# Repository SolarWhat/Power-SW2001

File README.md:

# Power-SW2001

Solar What?! is the outcome of ongoing research at the University of Edinburgh.

The product design process has taken place over three continents, with input from solar technicians, end users and energy access practitioners.

In 2017 over 6 million small, solar powered lighting devices were sold worldwide and 1.6 million solar powered lighting devices entered electronic waste flows.

We believe that delivering affordable, clean energy for all can also promote responsible production and consumption.

Our goal is to advocate for sustainable design in the global solar industry and promote the repair, reuse and recycling of solar powered electronics. We are pro-solar, anti-waste.

The Solar What?! Power is one of two products we have designed to champion our research and catalyse discussion around sustainability and repairability in the off-grid solar sector. The repository for our other product, the Solar What Light, can be found [here](https://github.com/SolarWhat/Light-SW1001 "here").

We encourage you to download the files, reproduce the products, make edits, suggest improvements and, most importantly, share your ideas around design for sustainable international development.  

More information about the project and the team behind it can be found on our [website](http://www.solarwhat.xyz/index.php "website").

You can get in touch with the team by emailing info@solarwhat.xyz. 

[User Manual and Tech Specs](http://www.solarwhat.xyz/resources.php "User Manual and Tech Specs")

[Gerber Files, BOM and Firmware Files](https://github.com/SolarWhat/Power-SW2001/tree/master/PCB%20Files "Gerber Files, BOM and Firmware Files")

[CAD Files (stp)](https://github.com/SolarWhat/Power-SW2001/blob/master/Solar%20What%20Power%20Assembly.stp "CAD Files (stp)")

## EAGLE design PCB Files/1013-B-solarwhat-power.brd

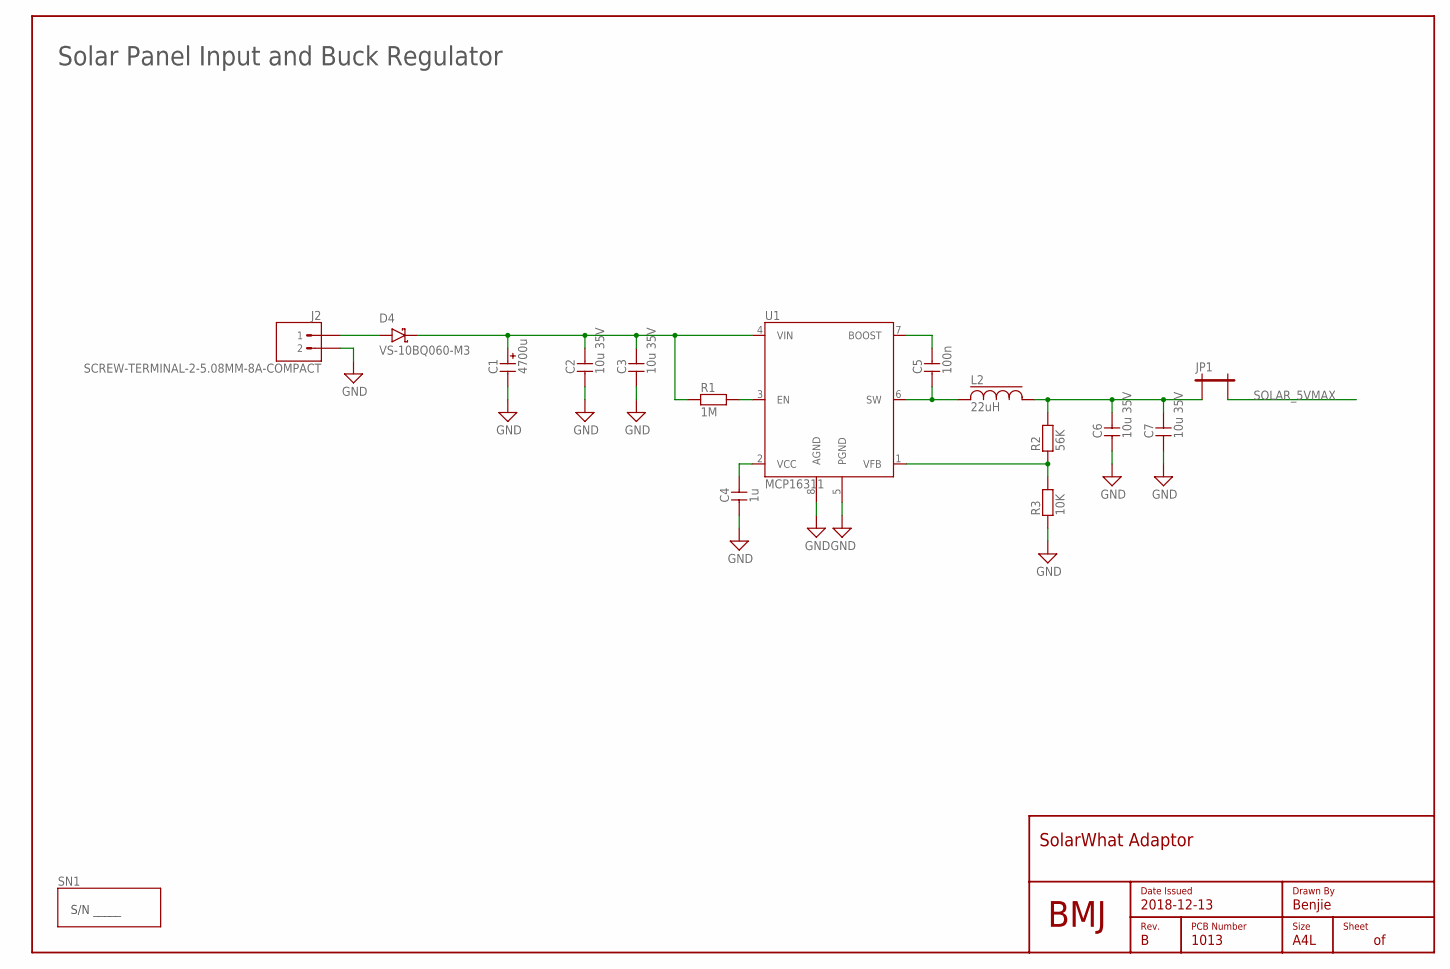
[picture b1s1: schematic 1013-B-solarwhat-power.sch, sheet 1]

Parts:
C1: 4700u; 18X36-TH-FLAT
C2, C3, C6, C7: 10u 35V; 1206
C4: 1u; 0805
C5: 100n; 0603
D4: VS-10BQ060-M3; SMB-ST
FRAME1: A4L-NEW; PCB-ID
J2: SCREW-TERMINAL-2-5.08MM-8A-COMPACT; CTBP0508/2
JP1: SOLDER-JUMPER-2MM
L2: 22uH; TDK-VLSX6045EX
LOGO1: BMJ-LOGO
R1: 1M; 0603
R2: 56K; 0603
R3: 10K; 0603
SN1: SERIAL-NUMBER-AREA; SERIAL-NUMBER-AREA-SMALL
U1: MCP16311; MSOP-8

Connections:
GND: C1.-, C2.1, C3.1, C4.1, C6.1, C7.1, J2.2, R3.1, U1.5 (PGND), U1.8 (AGND); also elsewhere on the board
unnamed: R1.2, U1.3 (EN)
unnamed: C1.+, C2.2, C3.2, D4.K (C), R1.1, U1.4 (VIN)
unnamed: C4.2, U1.2 (VCC)
unnamed: C5.2, U1.7 (BOOST)
unnamed: C5.1, L2.1, U1.6 (SW)
unnamed: D4.A, J2.1
unnamed: R2.1, R3.2, U1.1 (VFB)
unnamed: C6.2, C7.2, JP1.1, L2.2, R2.2
SOLAR_5VMAX: JP1.2; also elsewhere on the board

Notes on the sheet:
Solar Panel Input and Buck Regulator

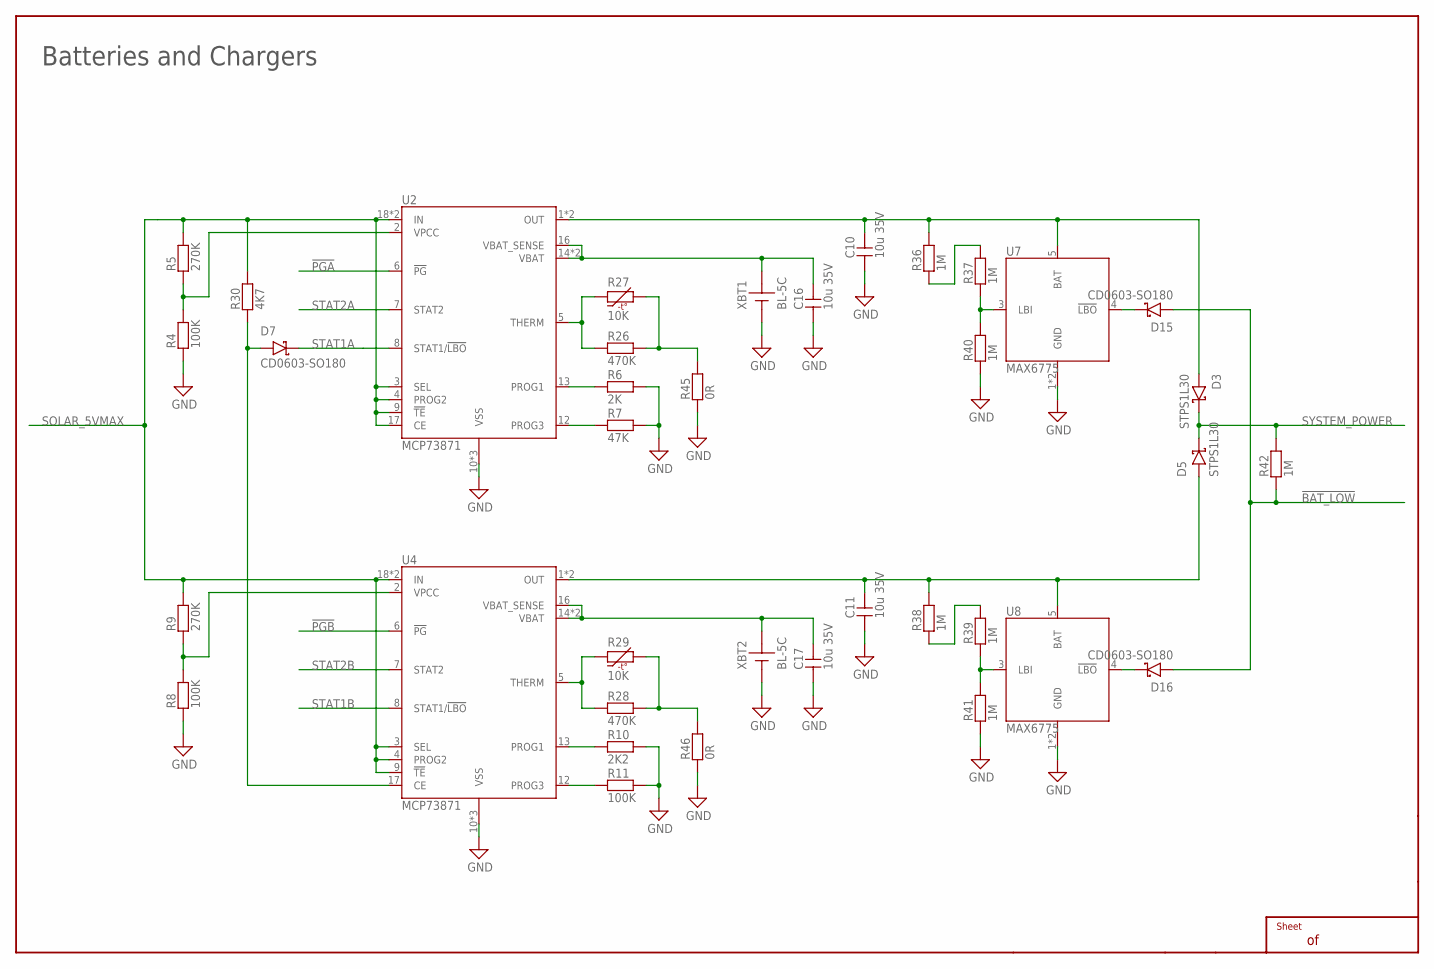
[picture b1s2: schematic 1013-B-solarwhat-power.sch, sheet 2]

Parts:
C10, C11, C16, C17: 10u 35V; 1206
D3, D5: STPS1L30; SMB-ST
D7, D15, D16: CD0603-SO180; 0603
FRAME2: A4L-CONTINUATION; EMPTY
R4, R8, R11: 100K; 0603
R5, R9: 270K; 0603
R6: 2K; 0603
R7: 47K; 0603
R10: 2K2; 0603
R26, R28: 470K; 0603
R27, R29: 10K; 0603
R30: 4K7; 0603
R36, R37, R38, R39, R40, R41, R42: 1M; 0603
R45, R46: 0R; 0603
U2, U4: MCP73871; QFN-20
U7, U8: MAX6775; SC70
XBT1, XBT2: BL-5C; 3MM-BATTERY-3WAY

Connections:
!BAT_LOW: D15.A, D16.A, R42.1; also elsewhere on the board
!PGA: U2.6 (!PG); also elsewhere on the board
!PGB: U4.6 (!PG); also elsewhere on the board
GND: C10.1, C11.1, C16.1, C17.1, R4.1, R6.2, R7.2, R8.1, R10.2, R11.2, R40.1, R41.1, R45.1, R46.1, U2.10 (VSS), U2.11 (VSS), U2.PAD (VSS), U4.10 (VSS), U4.11 (VSS), U4.PAD (VSS), U7.1 (GND), U7.2 (GND), U8.1 (GND), U8.2 (GND), XBT1.-, XBT2.-; also elsewhere on the board
unnamed: R4.2, R5.1, U2.2 (VPCC)
unnamed: R6.1, U2.13 (PROG1)
unnamed: R7.1, U2.12 (PROG3)
unnamed: C16.2, U2.14 (VBAT), U2.15 (VBAT), U2.16 (VBAT_SENSE), XBT1.+
unnamed: C10.2, D3.A, R36.2, U2.1 (OUT), U2.20 (OUT), U7.5 (BAT)
unnamed: R8.2, R9.1, U4.2 (VPCC)
unnamed: R10.1, U4.13 (PROG1)
unnamed: R11.1, U4.12 (PROG3)
unnamed: C17.2, U4.14 (VBAT), U4.15 (VBAT), U4.16 (VBAT_SENSE), XBT2.+
unnamed: C11.2, D5.A, R38.2, U4.1 (OUT), U4.20 (OUT), U8.5 (BAT)
unnamed: D7.A, R30.1, U4.17 (CE)
unnamed: R26.1, R27.1, U2.5 (THERM)
unnamed: R28.1, R29.1, U4.5 (THERM)
unnamed: R36.1, R37.2
unnamed: R37.1, R40.2, U7.3 (LBI)
unnamed: R38.1, R39.2
unnamed: R39.1, R41.2, U8.3 (LBI)
unnamed: D15.K (C), U7.4 (!LBO)
unnamed: D16.K (C), U8.4 (!LBO)
unnamed: R26.2, R27.2, R45.2
unnamed: R28.2, R29.2, R46.2
SOLAR_5VMAX: R5.2, R9.2, R30.2, U2.3 (SEL), U2.4 (PROG2), U2.9 (!TE), U2.17 (CE), U2.18 (IN), U2.19 (IN), U4.3 (SEL), U4.4 (PROG2), U4.9 (!TE), U4.18 (IN), U4.19 (IN); also elsewhere on the board
STAT1A: D7.K (C), U2.8 (STAT1/!LBO); also elsewhere on the board
STAT1B: U4.8 (STAT1/!LBO); also elsewhere on the board
STAT2A: U2.7 (STAT2); also elsewhere on the board
STAT2B: U4.7 (STAT2); also elsewhere on the board
SYSTEM_POWER: D3.K (C), D5.K (C), R42.2; also elsewhere on the board

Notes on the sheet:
Batteries and Chargers

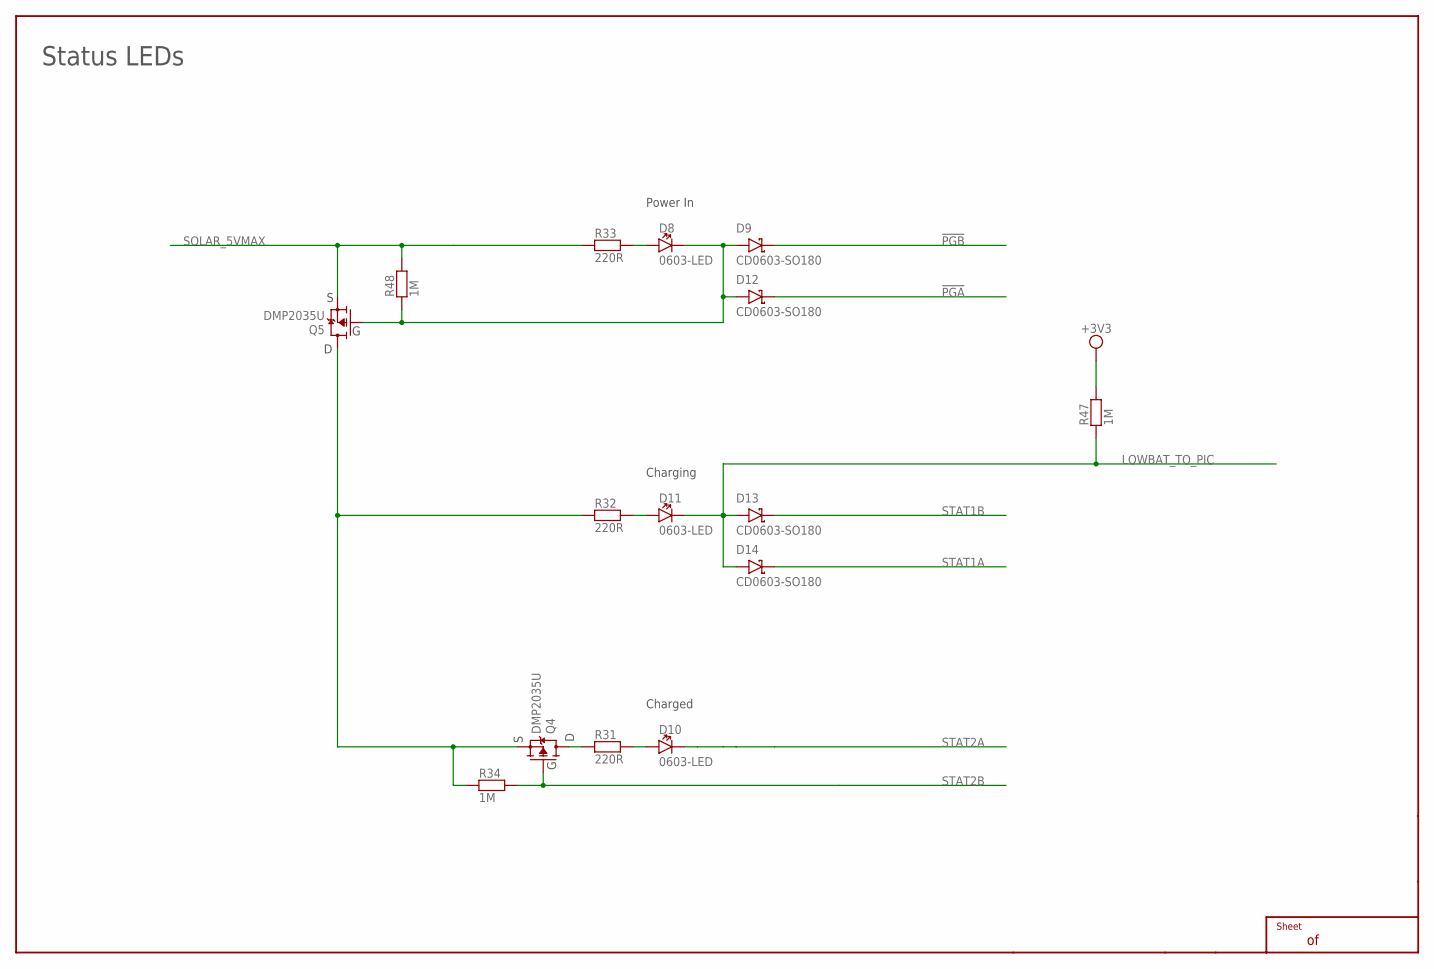
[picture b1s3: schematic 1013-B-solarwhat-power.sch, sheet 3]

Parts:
D8, D10, D11: 0603-LED
D9, D12, D13, D14: CD0603-SO180; 0603
FRAME5: A4L-CONTINUATION; EMPTY
Q4, Q5: DMP2035U; SOT-23
R31, R32, R33: 220R; 0603
R34, R47, R48: 1M; 0603

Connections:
!PGA: D12.K (C); also elsewhere on the board
!PGB: D9.K (C); also elsewhere on the board
+3V3: R47.2; also elsewhere on the board
GATED-LED-POWER: Q4.2 (S), Q5.3 (D), R32.1, R34.1
LOWBAT_TO_PIC: D11.C, D13.A, D14.A, R47.1; also elsewhere on the board
unnamed: D8.C, D9.A, D12.A, Q5.1 (G), R48.1
unnamed: Q4.3 (D), R31.1
unnamed: D10.A, R31.2
unnamed: D11.A, R32.2
unnamed: D8.A, R33.2
SOLAR_5VMAX: Q5.2 (S), R33.1, R48.2; also elsewhere on the board
STAT1A: D14.K (C); also elsewhere on the board
STAT1B: D13.K (C); also elsewhere on the board
STAT2A: D10.C; also elsewhere on the board
STAT2B: Q4.1 (G), R34.2; also elsewhere on the board

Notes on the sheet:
Power In
Charging
Charged
Status LEDs

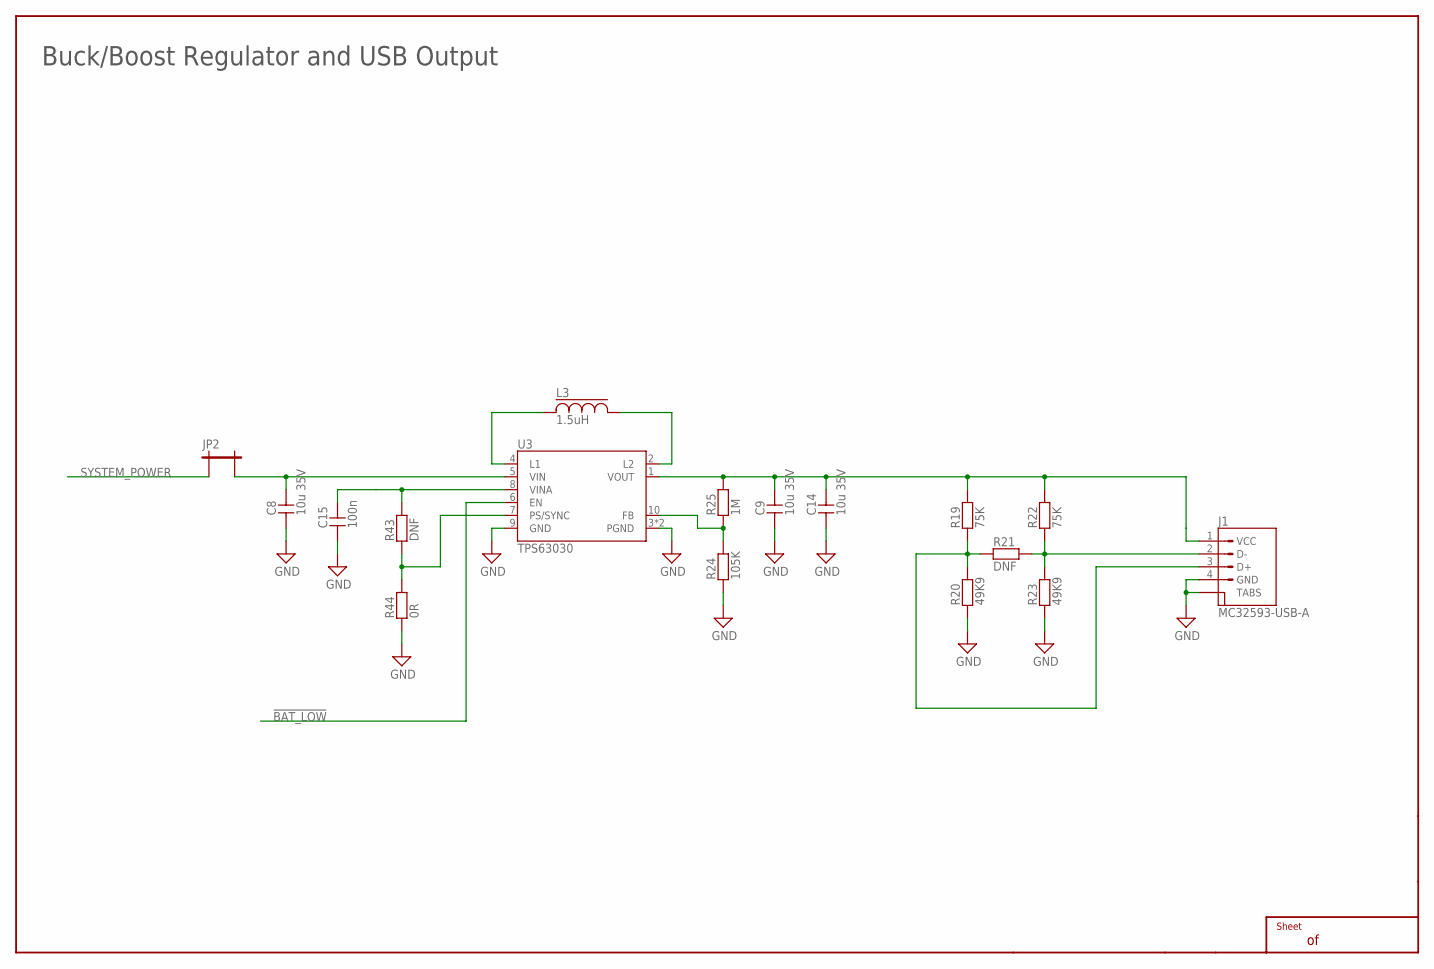
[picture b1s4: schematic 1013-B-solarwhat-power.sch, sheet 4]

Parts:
C8, C9, C14: 10u 35V; 1206
C15: 100n; 0603
FRAME3: A4L-CONTINUATION; EMPTY
J1: MC32593-USB-A; MC32593
JP2: SOLDER-JUMPER-2MM
L3: 1.5uH; TDK-VLSX5045EX
R19, R22: 75K; 0603
R20, R23: 49K9; 0603
R21, R43: DNF; 0603
R24: 105K; 0603
R25: 1M; 0603
R44: 0R; 0603
U3: TPS63030; VSON-10

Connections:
!BAT_LOW: U3.6 (EN); also elsewhere on the board
GND: C8.1, C9.1, C14.1, C15.1, J1.4 (GND), J1.TAB1 (TABS), J1.TAB2 (TABS), R20.1, R23.1, R24.1, R44.1, U3.3 (PGND), U3.9 (GND), U3.PAD (PGND); also elsewhere on the board
unnamed: J1.2 (D-), R21.2, R22.1, R23.2
unnamed: J1.3 (D+), R19.1, R20.2, R21.1
unnamed: L3.1, U3.4 (L1)
unnamed: L3.2, U3.2 (L2)
unnamed: C15.2, R43.2, U3.8 (VINA)
unnamed: R24.2, R25.1, U3.10 (FB)
unnamed: C9.2, C14.2, J1.1 (VCC), R19.2, R22.2, R25.2, U3.1 (VOUT)
unnamed: C8.2, JP2.2, U3.5 (VIN)
unnamed: R43.1, R44.2, U3.7 (PS/SYNC)
SYSTEM_POWER: JP2.1; also elsewhere on the board

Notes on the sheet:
Buck/Boost Regulator and USB Output

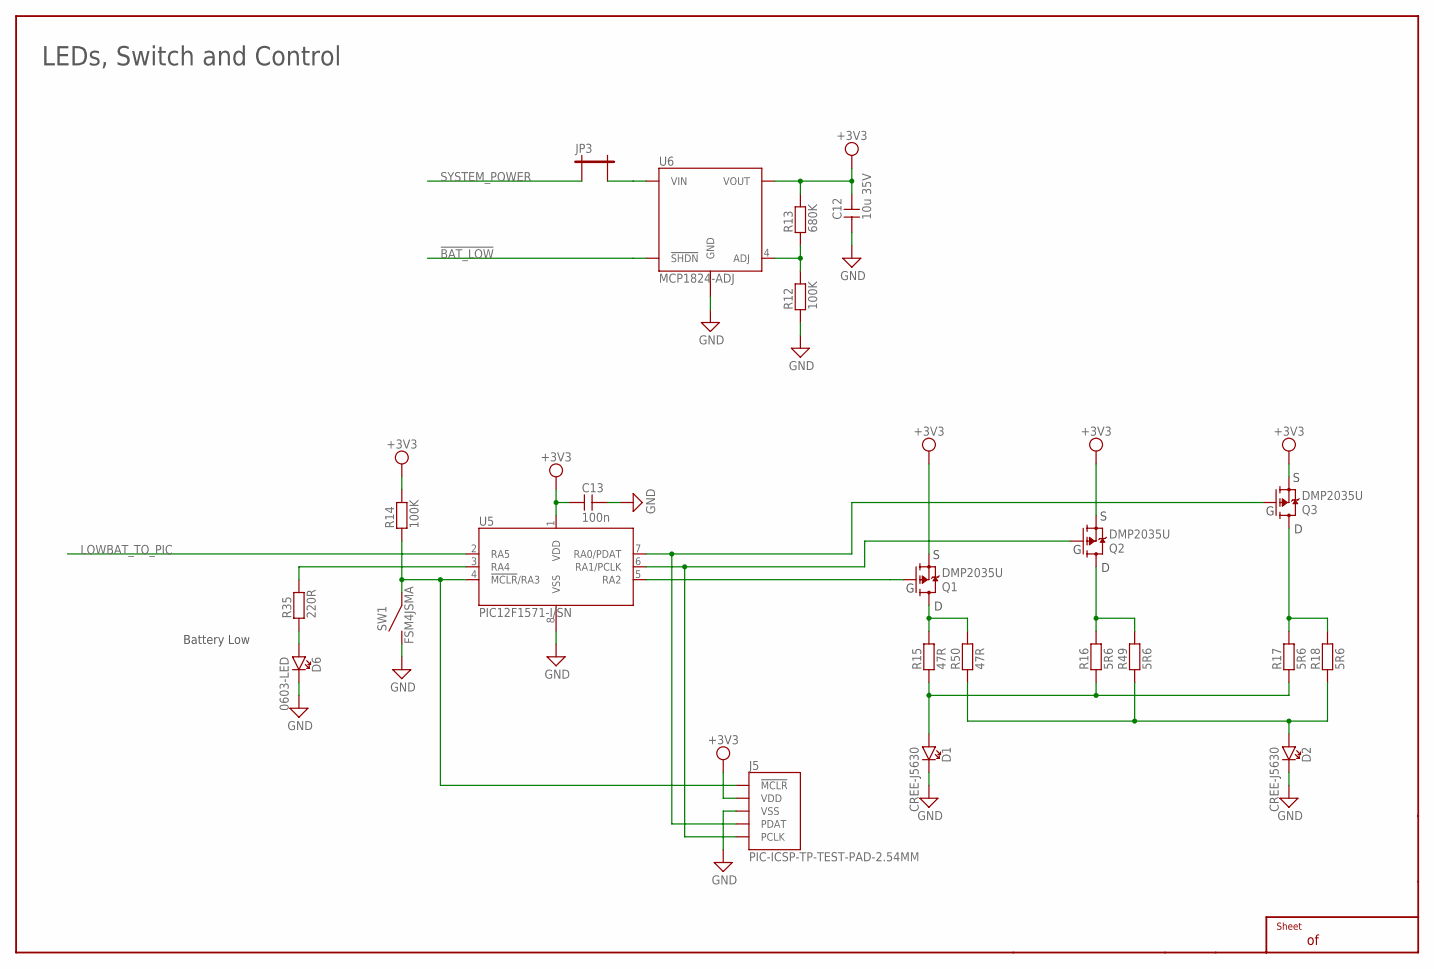
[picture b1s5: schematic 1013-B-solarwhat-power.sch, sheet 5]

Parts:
C12: 10u 35V; 1206
C13: 100n; 0603
D1, D2: CREE-J5630
D6: 0603-LED
FRAME4: A4L-CONTINUATION; EMPTY
J5: PIC-ICSP-TP-TEST-PAD-2.54MM; PIC-ICSP-TEST-PAD-2.54MM
JP3: SOLDER-JUMPER-2MM
Q1, Q2, Q3: DMP2035U; SOT-23
R12, R14: 100K; 0603
R13: 680K; 0603
R15, R50: 47R; 0603
R16, R17, R18, R49: 5R6; 0805
R35: 220R; 0603
SW1: FSM4JSMA; ALCOSWITCH-FSM4JSMA
U5: PIC12F1571-I/SN; SOIC-8
U6: MCP1824-ADJ; SOT-23-5

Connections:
!BAT_LOW: U6.3 (!SHDN); also elsewhere on the board
+3V3: C12.2, C13.1, J5.V+ (VDD), Q1.2 (S), Q2.2 (S), Q3.2 (S), R13.2, R14.2, U5.1 (VDD), U6.5 (VOUT); also elsewhere on the board
GND: C12.1, C13.2, D1.K (C), D2.K (C), D6.C, J5.GND (VSS), R12.1, SW1.1@1, SW1.1@2, U5.8 (VSS), U6.2 (GND); also elsewhere on the board
LOWBAT_TO_PIC: U5.2 (RA5); also elsewhere on the board
unnamed: J5.VPP (!MCLR), R14.1, SW1.2@1, SW1.2@2, U5.4 (!MCLR!/RA3)
unnamed: R12.2, R13.1, U6.4 (ADJ)
unnamed: D1.A, R15.1, R16.1, R17.1
unnamed: Q1.3 (D), R15.2, R50.2
unnamed: Q2.3 (D), R16.2, R49.2
unnamed: Q3.3 (D), R17.2, R18.2
unnamed: D2.A, R18.1, R49.1, R50.1
unnamed: J5.DAT, Q3.1 (G), U5.7 (RA0/PDAT)
unnamed: J5.CLK, Q2.1 (G), U5.6 (RA1/PCLK)
unnamed: Q1.1 (G), U5.5 (RA2)
unnamed: R35.2, U5.3 (RA4)
unnamed: JP3.2, U6.1 (VIN)
unnamed: D6.A, R35.1
SYSTEM_POWER: JP3.1; also elsewhere on the board

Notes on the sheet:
LEDs, Switch and Control
Battery Low

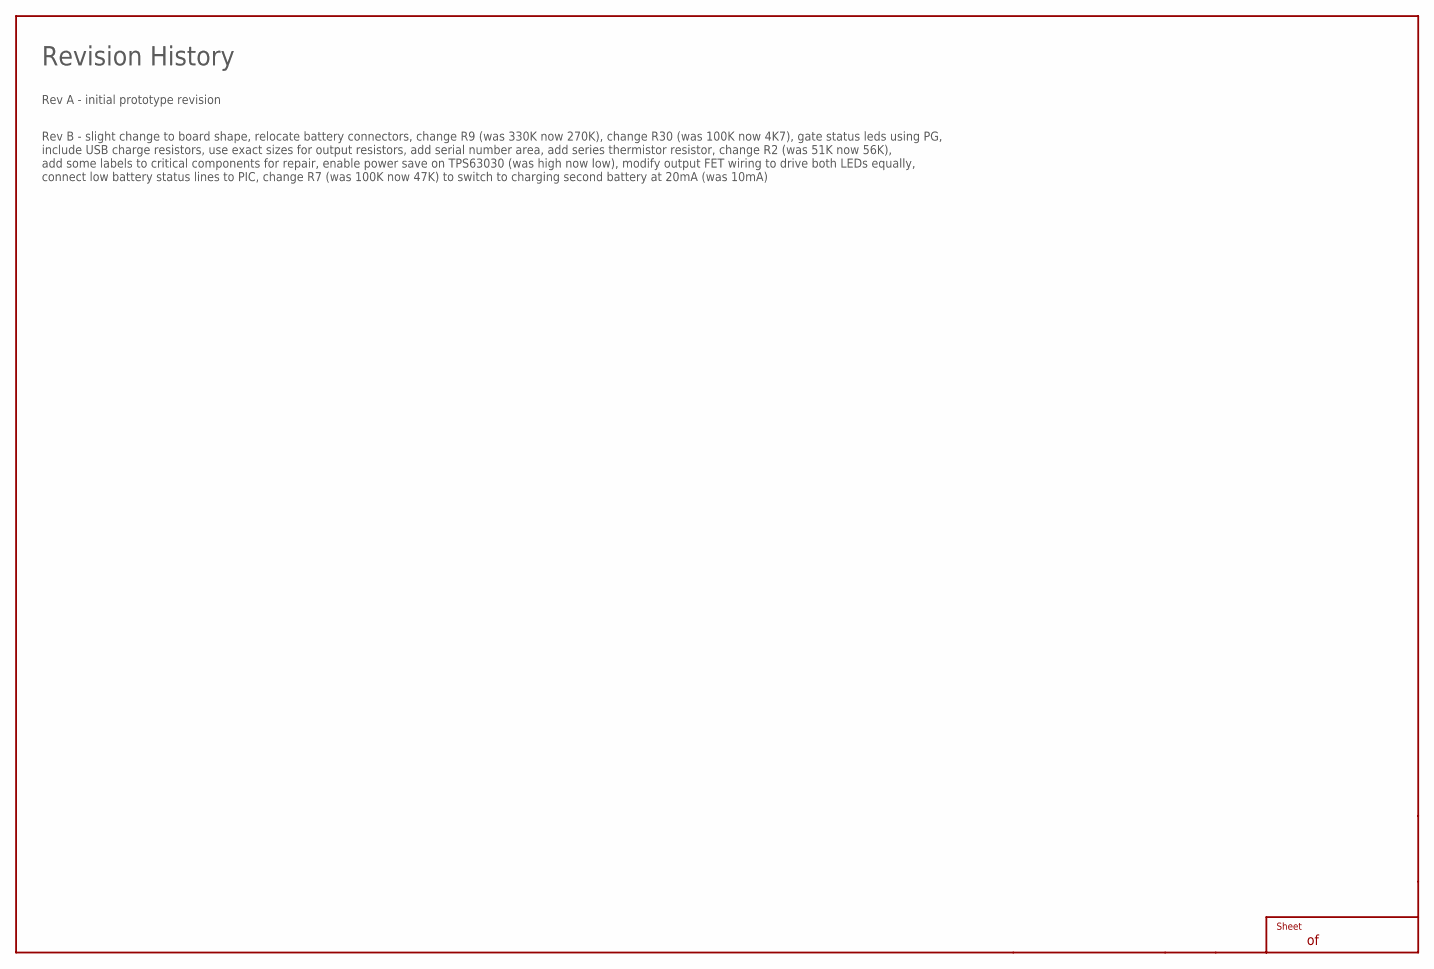
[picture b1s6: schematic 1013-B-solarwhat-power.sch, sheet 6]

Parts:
FRAME6: A4L-CONTINUATION; EMPTY

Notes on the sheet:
Revision History
Rev A - initial prototype revision
Rev B - slight change to board shape, relocate battery connectors, change R9 (was 330K now 270K), change R30 (was 100K now 4K7), gate status leds using PG, include USB charge resistors, use exact sizes for output resistors, add serial number area, add series thermistor resistor, change R2 (was 51K 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

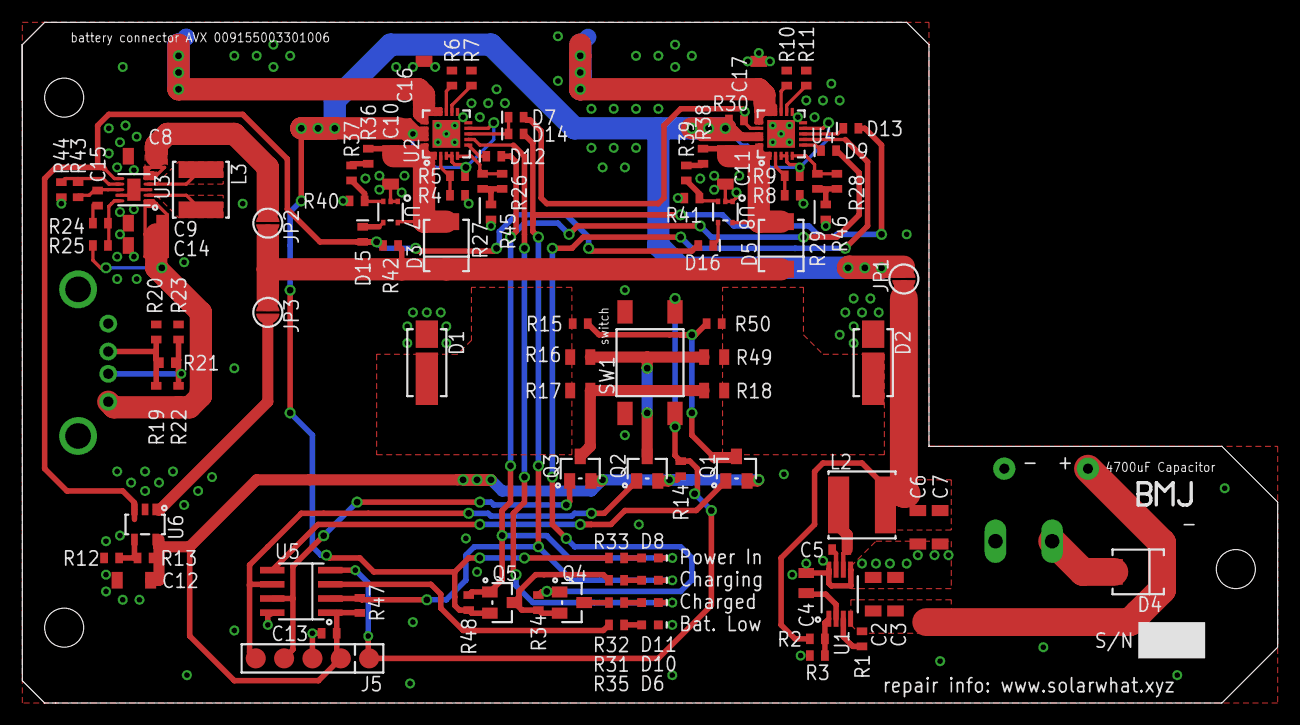
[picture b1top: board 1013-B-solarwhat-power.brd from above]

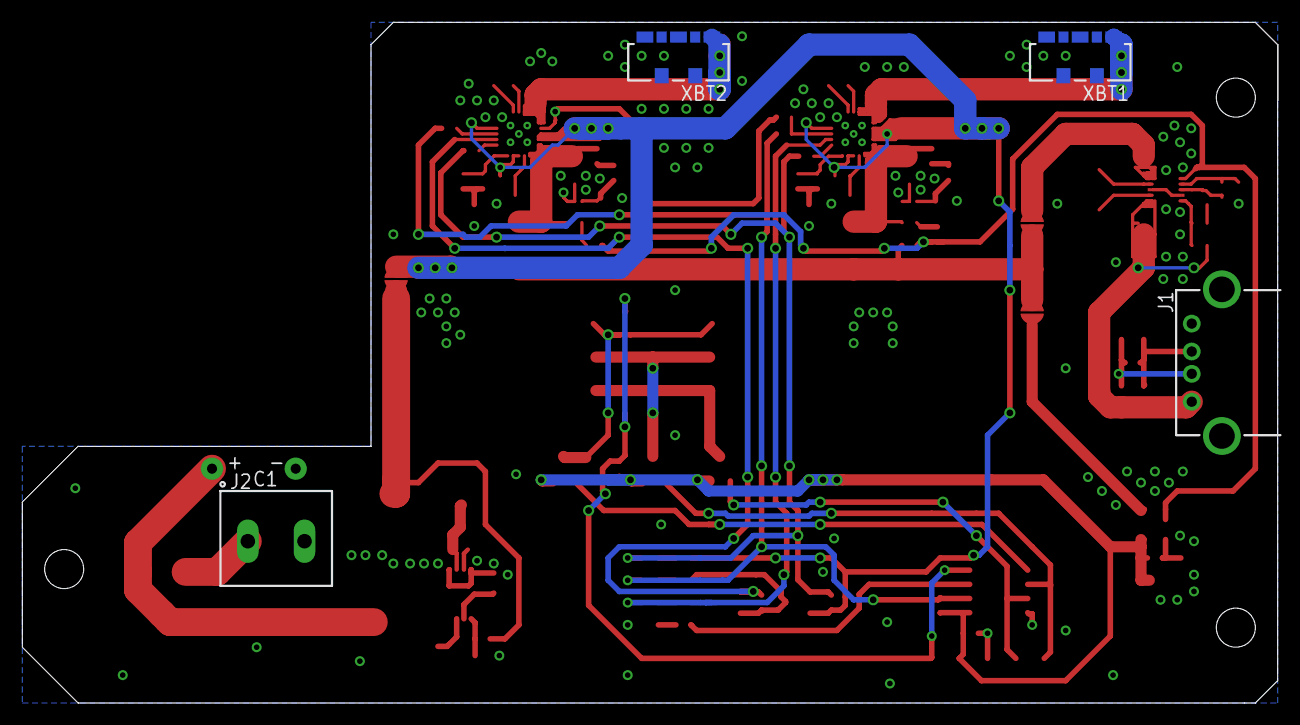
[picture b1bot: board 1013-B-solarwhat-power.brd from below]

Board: 2 copper layers, 112.5 x 61.0 mm, 115 parts (5 on the bottom side), 69 nets.

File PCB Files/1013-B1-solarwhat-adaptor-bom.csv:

"Component","Value","Manufacturer Part Number","Supplier Part Number","Description","Notes"
"C1",,"Panasonic ECA1VAM472X","Farnell 8767327",,
"C2","1206-10U-35V 10u 35V","1206 10uF 35V 10% X7R","standard",,
"C3","1206-10U-35V 10u 35V","1206 10uF 35V 10% X7R","standard",,
"C4","0805-1U 1u","0805 1uF 50V 10% X7R","standard",,
"C5","0603-100N 100n","0603 100nF 50V 10% X7R","standard",,
"C6","1206-10U-35V 10u 35V","1206 10uF 35V 10% X7R","standard",,
"C7","1206-10U-35V 10u 35V","1206 10uF 35V 10% X7R","standard",,
"C8","1206-10U-35V 10u 35V","1206 10uF 35V 10% X7R","standard",,
"C9","1206-10U-35V 10u 35V","1206 10uF 35V 10% X7R","standard",,
"C10","1206-10U-35V 10u 35V","1206 10uF 35V 10% X7R","standard",,
"C11","1206-10U-35V 10u 35V","1206 10uF 35V 10% X7R","standard",,
"C12","1206-10U-35V 10u 35V","1206 10uF 35V 10% X7R","standard",,
"C13","0603-100N 100n","0603 100nF 50V 10% X7R","standard",,
"C14","1206-10U-35V 10u 35V","1206 10uF 35V 10% X7R","standard",,
"C15","0603-100N 100n","0603 100nF 50V 10% X7R","standard",,
"C16","1206-10U-35V 10u 35V","1206 10uF 35V 10% X7R","standard",,
"C17","1206-10U-35V 10u 35V","1206 10uF 35V 10% X7R","standard",,
"D1",,"Cree JB5630AWT-C0-0000-000A0UC430E","Farnell 2853292",,
"D2",,"Cree JB5630AWT-C0-0000-000A0UC430E","Farnell 2853292",,
"D3",,"ST STPS1L30U","Farnell 1467550",,
"D4",,"Vishay VS-10BQ060-M3","Farnell 2628281",,
"D5",,"ST STPS1L30U","Farnell 1467550",,
"D6",,"Red 0603 LED","Farnell 2687488",,
"D7",,"RB751S40T1G","Farnell 2317437",,
"D8",,"Green 0603 LED","Farnell 2687486",,
"D9",,"RB751S40T1G","Farnell 2317437",,
"D10",,"Green 0603 LED","Farnell 2687486",,
"D11",,"Orange 0603 LED","Farnell 2687484",,
"D12",,"RB751S40T1G","Farnell 2317437",,
"D13",,"RB751S40T1G","Farnell 2317437",,
"D14",,"RB751S40T1G","Farnell 2317437",,
"D15",,"RB751S40T1G","Farnell 2317437",,"fit reversed relative to markings on board revision 1013-B!"
"D16",,"RB751S40T1G","Farnell 2317437",,"fit reversed relative to markings on board revision 1013-B!"
"J1",,"Multicomp MC32593","Farnell 1696534",,
"J2",,"CamdenBoss CTBP0508/2","Farnell 2668641",,
"JP1",,"SOLDER-JUMPER-2MM SOLDER-JUMPER-2MM","-",,"connect"
"JP2",,"SOLDER-JUMPER-2MM SOLDER-JUMPER-2MM","-",,"connect"
"JP3",,"SOLDER-JUMPER-2MM SOLDER-JUMPER-2MM","-",,"connect"
"L2","TDK-VLSX6045EX-220M 22uH","VLS6045EX-220M","Farnell 2493045",,
"L3","TDK-VLSX5045EX-3R3N 3.3uH","TDK VLS5045EX-3R3N","Farnell 2776741",,
"Q1",,"Diodes Inc DMP2035U","Farnell 2061419",,
"Q2",,"Diodes Inc DMP2035U","Farnell 2061419",,
"Q3",,"Diodes Inc DMP2035U","Farnell 2061419",,
"Q4",,"Diodes Inc DMP2035U","Farnell 2061419",,
"Q5",,"Diodes Inc DMP2035U","Farnell 2061419",,
"R1","0603-1%-1M 1M","0603 1M 1% 100mW","standard",,
"R2","0603-1%-56K 56K","0603 56K 1% 100mW","standard",,
"R3","0603-1%-10K 10K","0603 10K 1% 100mW","standard",,
"R4","0603-1%-100K 100K","0603 100K 1% 100mW","standard",,
"R5","0603-1%-270K 270K","0603 270K 1% 100mW","standard",,
"R6","0603-1%-2K2 2K2","0603 2.2K 1% 100mW","standard",,
"R7","0603-1%-47K 47K","0603 47K 1% 100mW","standard",,
"R8","0603-1%-100K 100K","0603 100K 1% 100mW","standard",,
"R9","0603-1%-270K 270K","0603 270K 1% 100mW","standard",,
"R10","0603-1%-2K2 2K2","0603 2.2K 1% 100mW","standard",,
"R11","0603-1%-100K 100K","0603 100K 1% 100mW","standard",,
"R12","0603-1%-100K 100K","0603 100K 1% 100mW","standard",,
"R13","0603-1%-680K 680K","0603 680K 1% 100mW","standard",,
"R14","0603-1%-100K 100K","0603 100K 1% 100mW","standard",,
"R15","0603-1%-47R 47R","0603 47R 1% 100mW","standard",,
"R16","0805 11R","0805 11R 1% 100mW","standard",,
"R17","0805 1R6","0805 1R6 1% 100mW","standard",,
"R18","0805 1R6","0805 1R6 1% 100mW","standard",,
"R19","0603-1%-75K 75K","0603 75K 1% 100mW","standard",,
"R20","0603-1%-49K9 49K9","0603 49K9 1% 100mW","standard",,
"R21","CHIP-0603-DNF DNF",,,,"Do Not Populate"
"R22","0603-1%-75K 75K","0603 75K 1% 100mW","standard",,
"R23","0603-1%-49K9 49K9","0603 49K9 1% 100mW","standard",,
"R24","0603-1%-110K 110K","0603 110K 1% 100mW","standard",,
"R25","0603-1%-1M 1M","0603 1M 1% 100mW","standard",,
"R26","0603-1%-470K 470K","0603 470K 1% 100mW","standard",,
"R27","NTC-0603-10K 10K","NCP18XH103F03RB 10K NTC Thermistor","Farnell 2456122",,
"R28","0603-1%-470K 470K","0603 470K 1% 100mW","standard",,
"R29","NTC-0603-10K 10K","NCP18XH103F03RB 10K NTC Thermistor","Farnell 2456122",,
"R30","0603-1%-4K7 4K7","0603 4.7K 1% 100mW","standard",,
"R31","0603-1%-220R 220R","0603 220R 1% 100mW","standard",,
"R32","0603-1%-220R 220R","0603 220R 1% 100mW","standard",,
"R33","0603-1%-220R 220R","0603 220R 1% 100mW","standard",,
"R34","0603-1%-1M 1M","0603 1M 1% 100mW","standard",,
"R35","0603-1%-220R 220R","0603 220R 1% 100mW","standard",,
"R36","0603-1%-1M 1M","0603 1M 1% 100mW","standard",,
"R37","0603-1%-1M 1M","0603 1M 1% 100mW","standard",,
"R38","0603-1%-1M 1M","0603 1M 1% 100mW","standard",,
"R39","0603-1%-1M 1M","0603 1M 1% 100mW","standard",,
"R40","0603-1%-1M 1M","0603 1M 1% 100mW","standard",,
"R41","0603-1%-1M 1M","0603 1M 1% 100mW","standard",,
"R42","CHIP-0603-DNF DNF",,,,"Do Not Populate"
"R43","CHIP-0603-DNF DNF",,,,"Do Not Populate"
"R44","0603-1%-0R 0R","0603 0R 1% 100mW","standard",,
"R45","0603-1%-0R 0R","0603 0R 1% 100mW","standard",,
"R46","0603-1%-0R 0R","0603 0R 1% 100mW","standard",,
"R47","0603-1%-1M 1M","0603 1M 1% 100mW","standard",,
"R48","0603-1%-1M 1M","0603 1M 1% 100mW","standard",,
"R49","0805 11R","0805 11R 1% 100mW","standard",,
"R50","0603-1%-47R 47R","0603 47R 1% 100mW","standard",,
"SW1",,"Alcoswitch FSM4JSMA","Farnell 3801305",,
"U1",,"Microchip MCP16311T-E/MS","Farnell 2857601",,
"U2",,"MCP73871-2CCI/ML","Farnell 1642489",,
"U3",,"TI TPS63030","Farnell 2781754",,
"U4",,"MCP73871-2CCI/ML","Farnell 1642489",,
"U5",,"Microchip PIC12F1571-I/SN","Farnell 2419682",,
"U6",,"MCP1824-ADJ SOT-23-5","Farnell 1578393",,
"U7",,"MAX6775XKB+T","Farnell 2799268",,
"U8",,"MAX6775XKB+T","Farnell 2799268",,
"XBT1",,"AVX 009155003301006","Digi-key 478-4687-1-ND",,
"XBT2",,"AVX 009155003301006","Digi-key 478-4687-1-ND",,

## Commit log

2019-09-15 Add files via upload
    Adding main image for Readme
2019-09-15 folder filler
2019-09-15 adding hero images
2019-09-15 changed image location
2019-09-15 readme changes
    adding text and links to light
2019-09-15 text edits
    text edits - adding solar what website
2019-09-15 Added future link reminders
2019-09-15 spelling
2019-09-15 Create filler
2019-09-15 Create test
2019-09-15 Rename test to test1
2019-09-15 adding pcb files
    adding all pub files in one place for ease of reference
2019-09-15 Create PCB Files
2019-09-15 Clean up folder
2019-09-15 Create LICENSE
2019-09-15 changing images folder
2020-11-18 Lighting Global ISM test results
